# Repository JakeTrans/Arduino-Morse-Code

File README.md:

# Arduino-Morse-Code
Morse code sound and letter view via 7 segment display via BlueTooth (arduino sketch plus Net core console app to communicate).  with Kicad project for a Arduino shield (UNO R3) - inculding Bluetooth connectivity and power pins on the PCB (going to Vin)

This project is a simple morse code sound with and 7-segment display to show the letter or number being sounded out using basic components.  the trimpot acts as a basic volume sontrol.

As part on this project I have used:

1 x 220ohm trimpot
8 x 1K resistors
1 x buzzer
1 x 5101AS 7 -segment display
1 x Ardinuo Uno R3

HC-05 Bluetooth Chip

for testing I powered the Ardinuo with a 9V battery clip although the Barrel Jack and other power solutions should work just as well (shield draws all power form the Arduino)

I've Included a Kicad project in the repo with a design for a shield which will require header pins as well, but makes the design more solid.

the .net core app include allows for communication over the serial port without the Arduino IDE.  It should autodetect a single arduino connected to the computer.

a Bluetooth serial App terminal will allow sending of data, I've used : Blue Serial Terminal from the Windows Store  and Ardiuno BLueconnect on Android to send commands.

When fully assembled the Bluetooth modules prevents programming so please remove the sheld if uploading code.

If Bluetooth or external power isn't required the parts don't need adding for the design to work.

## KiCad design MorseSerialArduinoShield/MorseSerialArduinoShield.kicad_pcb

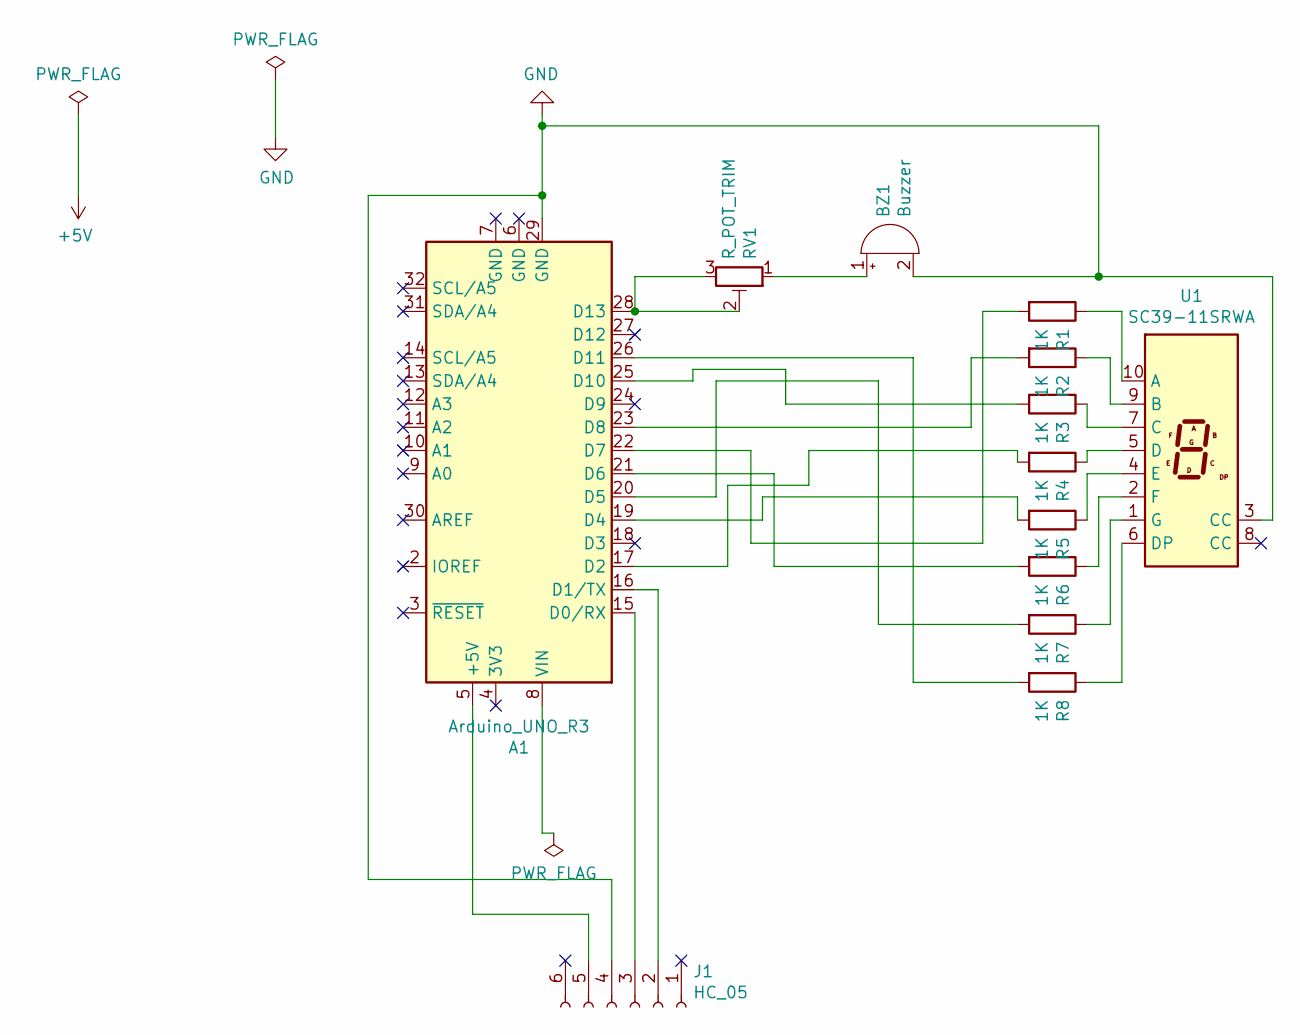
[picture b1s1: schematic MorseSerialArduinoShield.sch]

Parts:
A1: Arduino_UNO_R3
BZ1: Buzzer; Buzzer_12x9.5RM7.6
J1: HC_05; PinSocket_1x06_P2.54mm_Vertical
R1, R2, R3, R4, R5, R6, R7, R8: 1K; R_Axial_DIN0309_L9.0mm_D3.2mm_P12.70mm_Horizontal
RV1: R_POT_TRIM; Potentiometer_Runtron_RM-065_Vertical
U1: SC39-11SRWA; 7SegmentLED_LTS6760_LTS6780

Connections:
GND: A1.29 (GND), BZ1.2 (+), J1.4, U1.3 (CC); also elsewhere on the board
unnamed: A1.5 (+5V), J1.5
unnamed 8: A1.8 (VIN); also elsewhere on the board
unnamed: A1.15 (D0/RX), J1.3
unnamed: A1.16 (D1/TX), J1.2
unnamed: A1.17 (D2), R4.2
unnamed: A1.19 (D4), R5.2
unnamed: A1.20 (D5), R7.2
unnamed: A1.21 (D6), R6.2
unnamed: A1.22 (D7), R1.2
unnamed: A1.23 (D8), R2.2
unnamed: A1.25 (D10), R3.2
unnamed: A1.26 (D11), R8.2
unnamed: A1.28 (D13), RV1.2, RV1.3
unnamed: BZ1.1 (-), RV1.1
unnamed: R1.1, U1.10 (A)
unnamed: R2.1, U1.9 (B)
unnamed: R3.1, U1.7 (C)
unnamed: R4.1, U1.5 (D)
unnamed: R5.1, U1.4 (E)
unnamed: R6.1, U1.2 (F)
unnamed: R7.1, U1.1 (G)
unnamed: R8.1, U1.6 (DP)

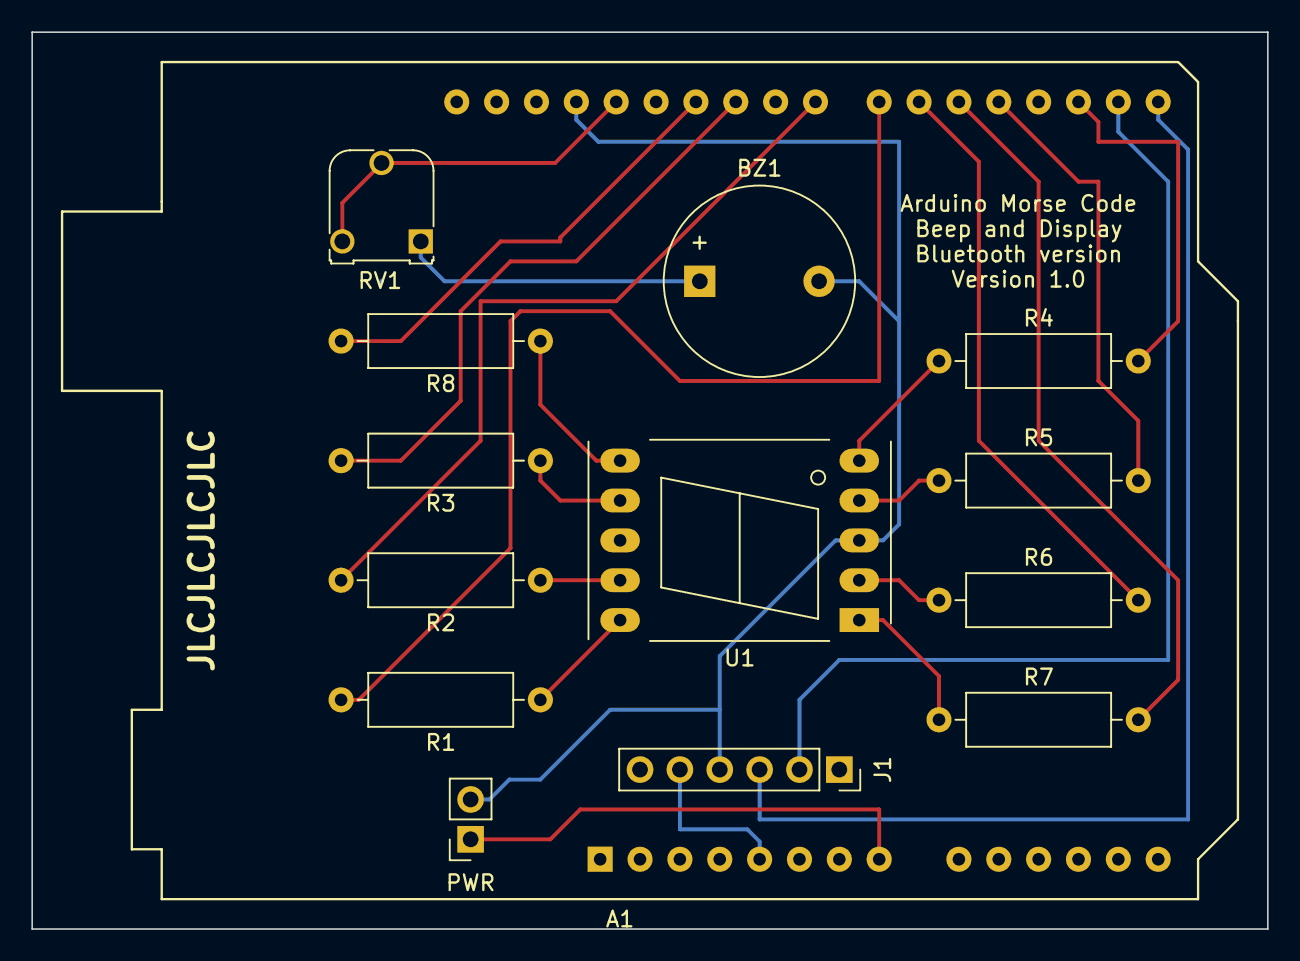
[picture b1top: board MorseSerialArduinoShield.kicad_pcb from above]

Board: 2 copper layers, 78.7 x 57.2 mm, 14 parts (1 on the bottom side), 23 nets.

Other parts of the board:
PWR: PWR and GND; PinSocket_1x02_P2.54mm_Vertical

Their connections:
GND: PWR.2; also elsewhere on the board
unnamed 8: PWR.1; also elsewhere on the board

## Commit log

2020-03-25 setup for net core console plus added sketch
2020-03-25 ports added, and inital code
2020-03-25 working morse code generation
2020-03-26 auto port finding
2020-03-29 second arduino project 8 segment
2020-04-05 Buzzer and dosplay version and changes
2020-04-05 full morse code put in
2020-04-05 Kicad start
2020-04-05 cleanup and error fixing
2020-04-10 Fixes
2020-05-31 Organised project
2020-05-31 base line wiring
2020-05-31 Removal of ardinuo template stuff
2020-05-31 ERC rules worrk
2020-06-04 pre pcb design
2020-06-06 BaseLine PCB design
2020-06-06 startpoint
2020-07-12 fright hand rework
2020-07-12 done design
2020-07-29 latest changes
2020-07-29 added arduino code
2020-08-01 pre pin re org
2020-08-01 pin corrected
2020-08-01 kicad layout fix
2020-08-01 re done efge cuts and values added
2020-08-09 .net core Console Added
2020-08-09 port spilt out
2020-08-09 auto detect com port
2020-08-09 Gerber removal
2020-08-10 Create LICENSE
    Added License file
2020-08-10 Create README.md
    Readme added
2020-09-24 Minor proposals
2021-11-27 Untested Bluetooth variant using HC-05
2021-11-28 Added external power pins for a battery and added JLC marker for production when ready
2022-02-13 refreshed Gerbers and reassignment of pins
2022-02-13 Update README.md
    expanded readme file
